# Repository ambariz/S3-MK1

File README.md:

# S3 MK-1

A compact Surveillance Security System built around a sensor-equipped cube and a wearable controller.

The S3 Cube monitors its surroundings using multiple sensors for motion, vibration, orientation, light, temperature, humidity, and sound. The data is sent to the S3 Watch, a small wearable controller with an OLED display and physical buttons for monitoring and controlling the cube.

The project includes custom PCBs designed in KiCad, custom component footprints, ESP8266 firmware, and fully 3D-printed enclosures designed in Onshape.

| S3 MK-1 Cube | S3 MK-1 Watch |
|-----------|------------|
|  |  |

# Features

- Wireless S3 Cube MK-1 to S3 Watch MK-1 communication
- Motion / Presence detection
- Vibration detection
- Tilt / Orientation detection
- Sound detection
- Light detection
- Temperature & Humidity monitoring
- OLED display
- Physical button controls
- Arm / Disarm system
- Status indication
- Custom KiCad PCBs
- Custom KiCad footprints
- ESP8266 firmware
- 3D-printed enclosures
- Weighted self-orienting cube design
- 20mm watch strap support

## CAD

> **Note:**
> S3 Cube MK-1 enclosure is made for rolling in a plain surface. This's the reason the edges are with R10.

| S3 Cube MK-1 | S3 Watch MK-1 |
|------|-------|
|  |  |
|  |  |

## PCB

> **Note:**  
> The S3 Watch PCB is designed with a 20mm strap support, If you are 3D printing the enclosure for the watch, Feel free to break it with pliers.

| S3 MK-1 Cube PCB | S3 MK-1 Watch PCB |
|-----------|------------|
|  |  |
|  |  |

## Schematic

> **Note:**  
> The preview images may be scaled down and lose detail. Use the journal.md for a clear, full-resolution view.

| S3 MK-1 Cube | S3 MK-1 Watch |
|-----------|------------|
|  |  |

## BOM

| Product | Quantity | Source | Price (INR) | Link |
| :--- | :--- | :--- | :--- | :--- |
| D1 Mini ESP8266 | 2 | Robu | 199 | [Product Link](https://robu.in/product/d1-mini-v2-nodemcu-4m-bytes-lua-wifi-internet-of-things-development-board-based-esp8266/) |
| mmWave Sensor HLK-LD2410-AA | 1 | Robu | 639 | [Product Link](https://robu.in/product/hi-link-hlk-ld2410s/) |
| SW-420 Vibration Sensor Module | 1 | Robu | 42 | [Product Link](https://robu.in/product/vibration-sensor-module-alarm-motion-sensor-module-vibration-switch-sw-420/) |
| MPU-6050 3-Axis Accelerometer and Gyro Sensor | 1 | Robu | 154 | [Product Link](https://robu.in/product/mpu-6050-gyro-sensor-2-accelerometer/) |
| LDR 5mm | 1 | Robu | 59 | [Product Link](https://robu.in/product/1-month-warranty-1307/) |
| DHT11 | 1 | Robu | 51 | [Product Link](https://robu.in/product/dht11-digital-relative-humidity-temperature-sensor-module/) |
| LiPo Battery | 2 | Robu | 219 | [Product Link](https://robu.in/product/400mah-pcm-protected-micro-li-po-battery/) |
| Slide Switch | 2 | Robu | 2 | [Product Link](https://robu.in/product/1-month-warranty-255/) |
| Neopixel 5050 | 2 | Robu | 176 | [Product Link](https://robu.in/product/ws2812b-rgb-addressable-led-module/) |
| Buzzer | 2 | Robu | 47 | [Product Link](https://robu.in/product/1-month-warranty-1248/) |
| Tactile Push Button Switch | 4 | Robu | 1.26 | [Product Link](https://robu.in/product/6x6x5mm-tactile-push-button-switch-pack-of-20/) |
| ERM Coin Vibration Motor | 1 | Robu | 77 | [Product Link](https://robu.in/product/erm-coin-vibration-motor-d10mm-w-3-4mm/) |

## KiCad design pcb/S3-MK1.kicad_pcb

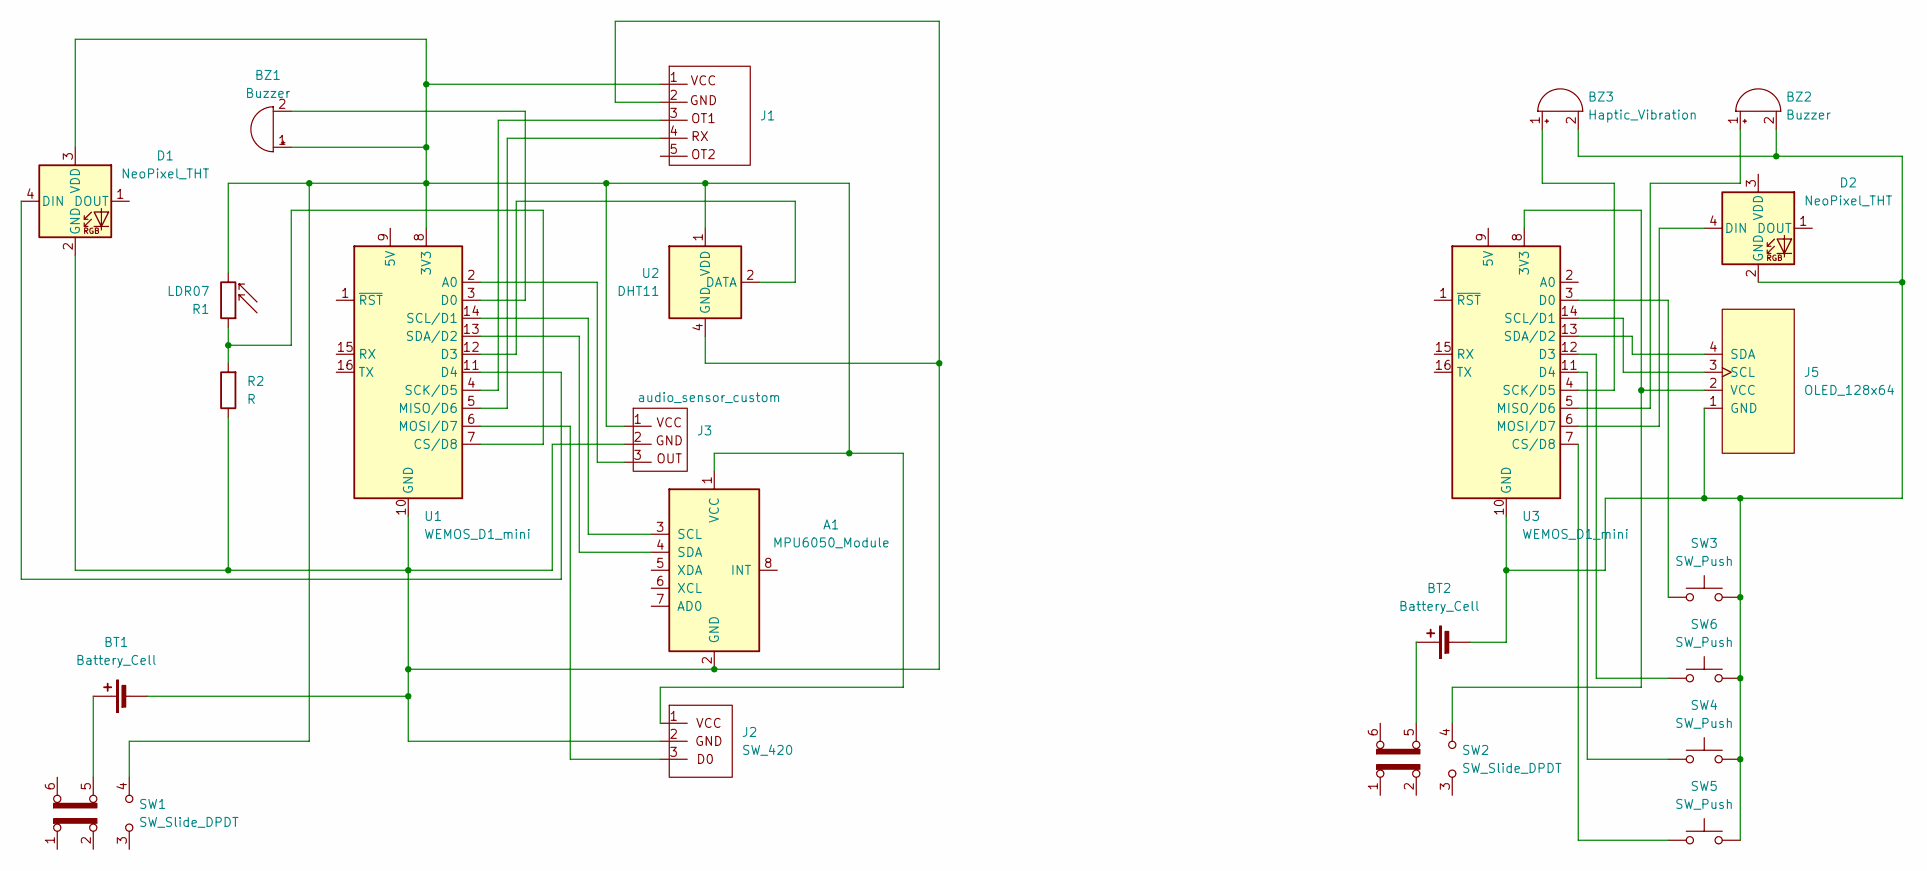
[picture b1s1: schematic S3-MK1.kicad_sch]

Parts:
A1: MPU6050_Module
BT1, BT2: Battery_Cell; Battery_LiPo_Custom
BZ1: Buzzer; Buzzer_TDK_PS1240P02BT_D12.2mm_H6.5mm
BZ2: Buzzer; MagneticBuzzer_Kingstate_KCG0601
BZ3: Haptic_Vibration; MagneticBuzzer_Kingstate_KCG0601
D1, D2: NeoPixel_THT; LED_SK6812_PLCC4_5.0x5.0mm_P3.2mm
J1: LD2420_custom
J2: SW_420; Vibration_sensor_SW420_custom
J3: audio_sensor_custom; Audio_sensor_custom
J5: OLED_128x64
R1: LDR07; R_LDR_5.1x4.3mm_P3.4mm_Vertical
R2: R; R_Axial_DIN0204_L3.6mm_D1.6mm_P5.08mm_Horizontal
SW1, SW2: SW_Slide_DPDT; SW_CK_JS202011CQN_DPDT_Straight
SW3, SW4, SW5, SW6: SW_Push; SW_PUSH_1P1T_6x3.5mm_H4.3_APEM_MJTP1243
U1, U3: WEMOS_D1_mini; WEMOS_D1_mini_light
U2: DHT11; Aosong_DHT11_5.5x12.0_P2.54mm

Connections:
unnamed: A1.2 (GND), BT1.2 (-), D1.2 (GND), J1.2 (GND), J2.2 (GND), J3.2, R2.1, U1.10 (GND), U2.4 (GND)
unnamed: A1.3 (SCL), U1.14 (SCL/D1)
unnamed: A1.4 (SDA), U1.13 (SDA/D2)
unnamed: A1.1 (VCC), BZ1.1 (+), D1.3 (VDD), J1.1 (VCC), J2.1 (VCC), J3.1, R1.2, SW1.4 (A), U1.8 (3V3), U2.1 (VDD)
unnamed: BT1.1 (+), SW1.5 (B)
unnamed: BT2.1 (+), SW2.5 (B)
unnamed: BT2.2 (-), BZ2.2 (-), BZ3.2 (-), D2.2 (GND), J5.1 (GND), SW3.2, SW4.2, SW5.2, SW6.2, U3.10 (GND)
unnamed: BZ1.2 (-), U1.3 (D0)
unnamed: BZ2.1 (+), U3.5 (MISO/D6)
unnamed: BZ3.1 (+), U3.4 (SCK/D5)
unnamed: D1.4 (DIN), U1.11 (D4)
unnamed: D2.4 (DIN), U3.6 (MOSI/D7)
unnamed: J1.4, U1.5 (MISO/D6)
unnamed: J1.3 (RX), U1.4 (SCK/D5)
unnamed: J2.3 (D0), U1.6 (MOSI/D7)
unnamed: J3.3, U1.2 (A0)
unnamed: J5.3 (SCL), U3.14 (SCL/D1)
unnamed: J5.4 (SDA), U3.13 (SDA/D2)
unnamed: J5.2 (VCC), SW2.4 (A), U3.8 (3V3)
unnamed: R1.1, R2.2, U1.7 (CS/D8)
unnamed: U1.12 (D3), U2.2 (DATA)
unnamed: SW5.1, U3.7 (CS/D8)
unnamed: SW3.1, U3.3 (D0)
unnamed: SW6.1, U3.12 (D3)
unnamed: SW4.1, U3.11 (D4)

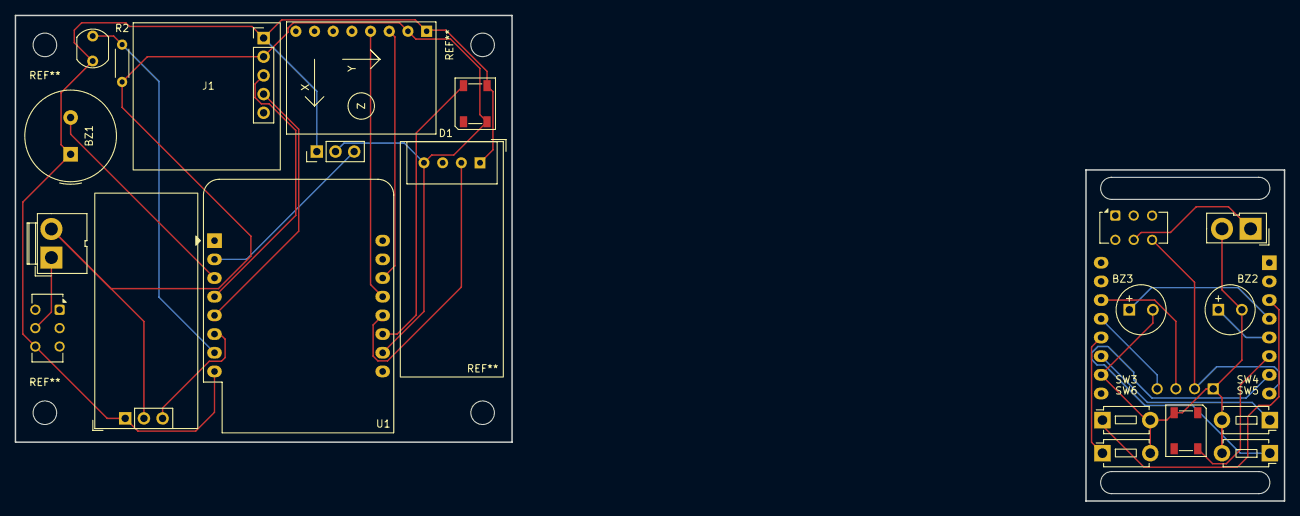
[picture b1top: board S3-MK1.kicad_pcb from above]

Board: 2 copper layers, 172.5 x 66.0 mm, 23 parts (1 on the bottom side), 25 nets.

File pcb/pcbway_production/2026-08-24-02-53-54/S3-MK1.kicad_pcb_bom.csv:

Designator,Quantity,Value,Footprint,Package,MPN,DNP,Mount_Type,Description,Sim.Device,Sim.Type,Sim.Pins,KiLib_Generator
A1,1,MPU6050_Module,MPU6050_Module,,,,tht,,,,,
"BT1, BT2",2,Battery_Cell,Battery_LiPo_Custom,,,,tht,Single-cell battery,V,DC,1=+ 2=-,
BZ1,1,Buzzer,Buzzer_TDK_PS1240P02BT_D12.2mm_H6.5mm,,,,tht,"Buzzer, polarized",,,,
BZ2,1,Buzzer,MagneticBuzzer_Kingstate_KCG0601,,,,tht,"Buzzer, polarized",,,,
BZ3,1,Haptic_Vibration,MagneticBuzzer_Kingstate_KCG0601,,,,tht,Vibration,,,,
"D1, D2",2,NeoPixel_THT,LED_SK6812_PLCC4_5.0x5.0mm_P3.2mm,,,,smt,"RGB LED with integrated controller, 5mm/8mm LED package",,,,
J1,1,~,LD2420_custom,,,,tht,HLK LD2420,,,,
J2,1,SW_420,Vibration_sensor_SW420_custom,,,,tht,,,,,
J3,1,audio_sensor_custom,Audio_sensor_custom,,,,tht,,,,,
J5,1,OLED_128x64,OLED_128x64,,,,tht,,,,,
R1,1,LDR07,R_LDR_5.1x4.3mm_P3.4mm_Vertical,,,,tht,light dependent resistor,,,,
R2,1,R,R_Axial_DIN0204_L3.6mm_D1.6mm_P5.08mm_Horizontal,,,,tht,Resistor,,,,resistor/THT
"SW1, SW2",2,SW_Slide_DPDT,SW_CK_JS202011CQN_DPDT_Straight,,,,tht,"Slide Switch, dual pole double throw",,,,
"SW3, SW4, SW5, SW6",4,SW_Push,SW_PUSH_1P1T_6x3.5mm_H4.3_APEM_MJTP1243,,,,tht,"Push button switch, generic, two pins",,,,
"U1, U3",2,WEMOS_D1_mini,WEMOS_D1_mini_light,,,,tht,32-bit microcontroller module with WiFi,,,,
U2,1,DHT11,Aosong_DHT11_5.5x12.0_P2.54mm,,,,tht,"3.3V to 5.5V, temperature and humidity module, DHT11",,,,
